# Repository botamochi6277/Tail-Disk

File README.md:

# Tail Disk

PCB Design of a board for [Hacka-Tail](https://botalab.tech/hacka-tail/) with EAGLE.

You can put the board in [DAISO drink bottles](https://www.daisonet.com/product/4549131644531).

These items are on the board.

- Piezo speaker
- Microphone
- IMU Module (MPU9250)

The board has connecters with:

- PWM Servo motor x2
- Batteries (JST PH)
- Controller Module (MIL Connector)

## LICENCE

[OPEN SOURCE HARDWARE](https://www.oshwa.org/definition/)

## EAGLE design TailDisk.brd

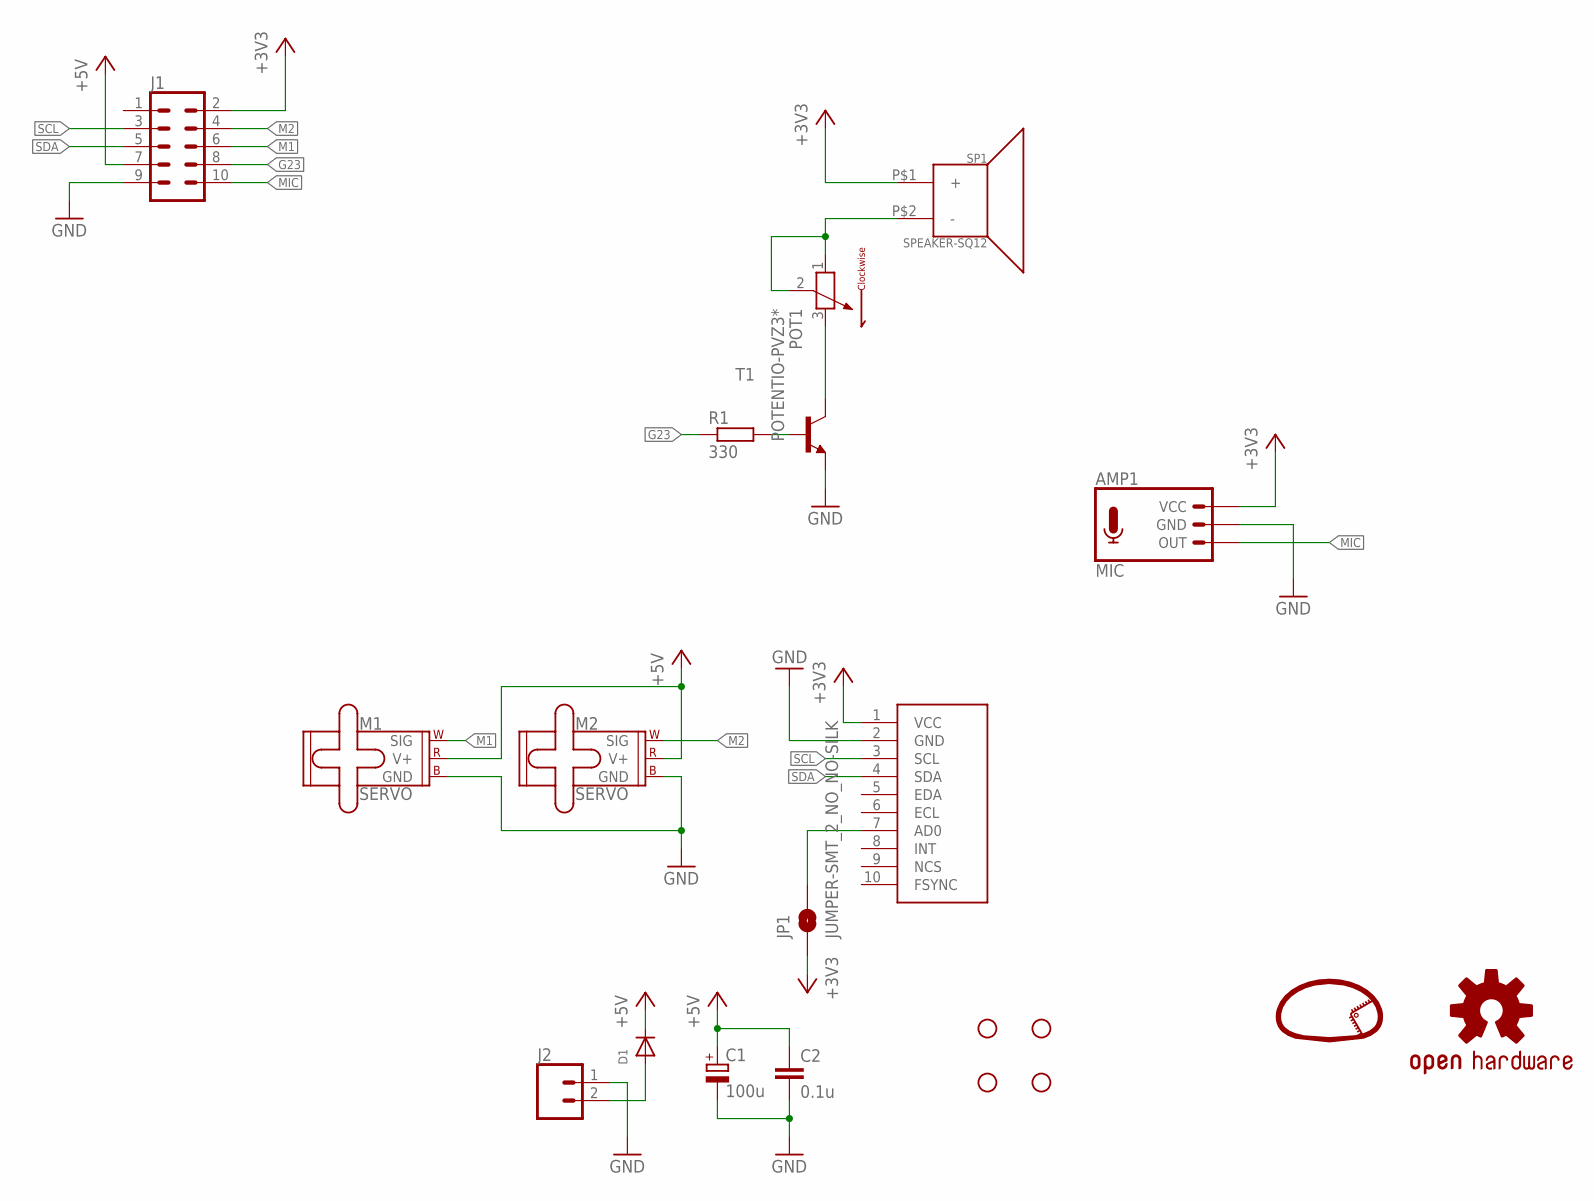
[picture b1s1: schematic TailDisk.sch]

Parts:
AMP1: MIC; ADAFRUIT-1063
C1: 100u; 153CLV-0605
C2: 0.1u; C1608
D1: DIODE_SOD-123FL; SOD-123FL
H1, H2, H3, H4: STAND-OFF3.3; STAND-OFF-3.3
IC1: IMU-MODULE
J1: CONN_05X2RA; 2X5-RA
J2: CONN_02-JST-2MM-SMT; JST-2-SMD
JP1: JUMPER-SMT_2_NO_NO-SILK; SMT-JUMPER_2_NO_NO-SILK
LOGO1: LOGO
LOGO2: OSHW-LOGOS; OSHW-LOGO-S
M1, M2: SERVO; 1X03
POT1: POTENTIO-PVZ3*; PVZ3*
R1: 330; R0603
SP1: SPEAKER-SQ12; PKLCS1212E
T1: MMUN2211LT1-NPN-SC59-BEC; SC59-BEC

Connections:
+3V3: AMP1.P$3 (VCC), IC1.1 (VCC), J1.2, JP1.1, SP1.P$1 (+)
+5V: C1.+, C2.1, D1.C, J1.7, M1.2 (V+), M2.2 (V+)
G23: J1.8, R1.1
GND: AMP1.P$2 (GND), C1.-, C2.2, IC1.2 (GND), J1.9, J2.1 (2), M1.3 (GND), M2.3 (GND), T1.E
M1: J1.6, M1.1 (SIG)
M2: J1.4, M2.1 (SIG)
MIC: AMP1.P$1 (OUT), J1.10
unnamed: IC1.7 (AD0), JP1.2
unnamed: POT1.1, POT1.2, SP1.P$2 (-)
unnamed: POT1.3, T1.C
unnamed: R1.2, T1.B
unnamed: D1.A, J2.2 (1)
SCL: IC1.3 (SCL), J1.3
SDA: IC1.4 (SDA), J1.5

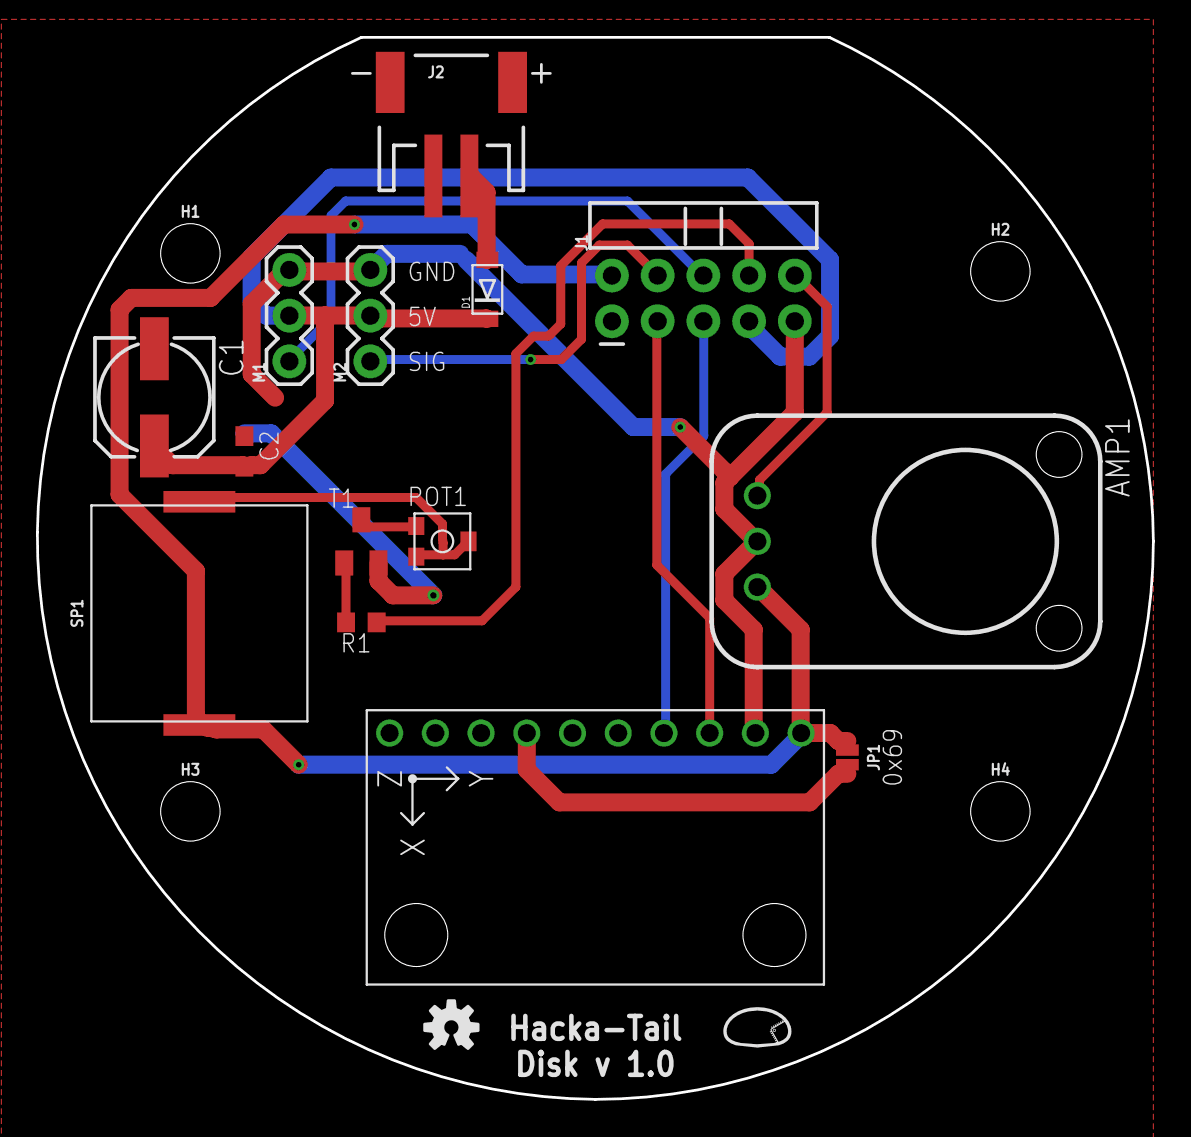
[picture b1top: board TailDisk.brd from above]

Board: 2 copper layers, 62.0 x 59.0 mm, 20 parts (0 on the bottom side), 14 nets.

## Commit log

2021-06-28 rev_01
2021-08-28 update brd
2021-08-28 add readme

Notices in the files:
parts and their libraries:
SparkFun-Aesthetics: Licensing: Creative Commons ShareAlike 4.0 International - https://creativecommons.org/licenses/by-sa/4.0
